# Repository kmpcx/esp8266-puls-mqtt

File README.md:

ESP8266 Sketch for potential free contact sensor
======================

This sketch is meant to let you detecd pulses on a potential free contact and send them via an asyncronous connection to a MQTT broker.
It can be used to monitor every kind of binary state. It can be used to detect machine cycles (counting parts), states of windows to observe if they are closed properly or any relay you can possibly think of.

## Table of content
- [Setup](#setup)
    - [WiFi](#wifi)
    - [MQTT](#mqtt)
    - [OTA](#ota)
- [PCB](#pcb)

## Setup

All the setup is done in the config file. You can create own config files for different locations/environment.

### WiFi

```
#define WIFI_SSID "SSID"
#define WIFI_PASSWORD "Password"

bool IPStatic = false; // true if it is a static IP
IPAddress staticIP(10,49,13,103); //ESP static ip
IPAddress gateway(10,49,13,1);   //IP Address of your WiFi Router (Gateway)
IPAddress subnet(255, 255, 255, 0);  //Subnet mask
IPAddress dns(10,49,13,1);  //DNS
```

### MQTT

You need to define your MQTT broker.
The MQTT Topics are defined in the main.ccp file.

```
#define MQTT_HOST IPAddress(0, 0, 0, 0)
#define MQTT_PORT 1883
#define MQTT_SECURE true
#define MQTT_USERNAME "USER"
#define MQTT_PASSWORD "PASSWORD"
```

### OTA

You need to define a location where the micro controller should ask for a update binary file.

```
#define updateServer "http://location.loc/"
```

## PCB

We designed a PCB board which fits perfectly the need for a potential free contact sensor.
The source for it is located in the PCB folder.

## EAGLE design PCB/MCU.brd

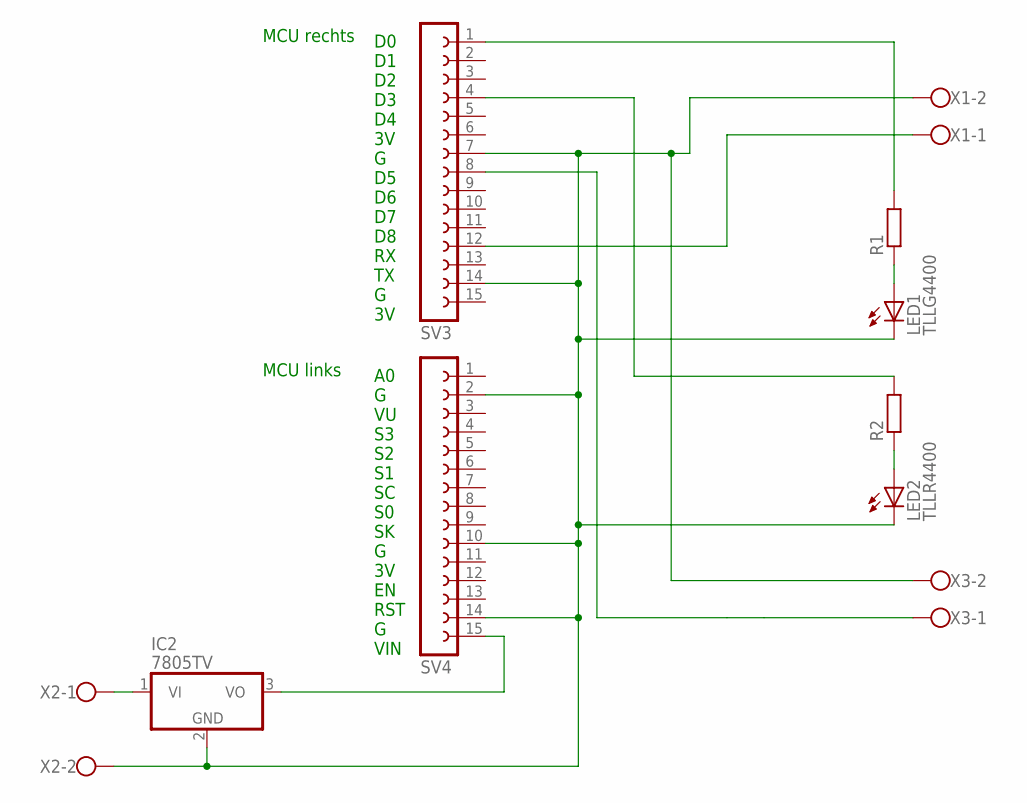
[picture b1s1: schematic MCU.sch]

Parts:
IC2: 7805TV; TO220V
LED1: TLLG4400; LED3MM
LED2: TLLR4400; LED3MM
R1, R2: R0207/10; 0207/10
SV3, SV4: FE15-1; FE15
X1, X2, X3: W237-102

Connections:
G: IC2.2 (GND), LED1.K (C), LED2.K (C), SV3.7, SV3.14, SV4.2, SV4.10, SV4.14, X1.2, X2.2, X3.2
unnamed: IC2.1 (VI), X2.1
unnamed: SV3.12, X1.1
unnamed: SV3.8, X3.1
unnamed: LED2.A, R2.1
unnamed: LED1.A, R1.1
unnamed: R1.2, SV3.1
unnamed: R2.2, SV3.4
unnamed: IC2.3 (VO), SV4.15

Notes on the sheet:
MCU rechts
MCU links
A0 G VU S3 S2 S1 SC S0 SK G 3V EN RST G VIN
D0 D1 D2 D3 D4 3V G D5 D6 D7 D8 RX TX G 3V

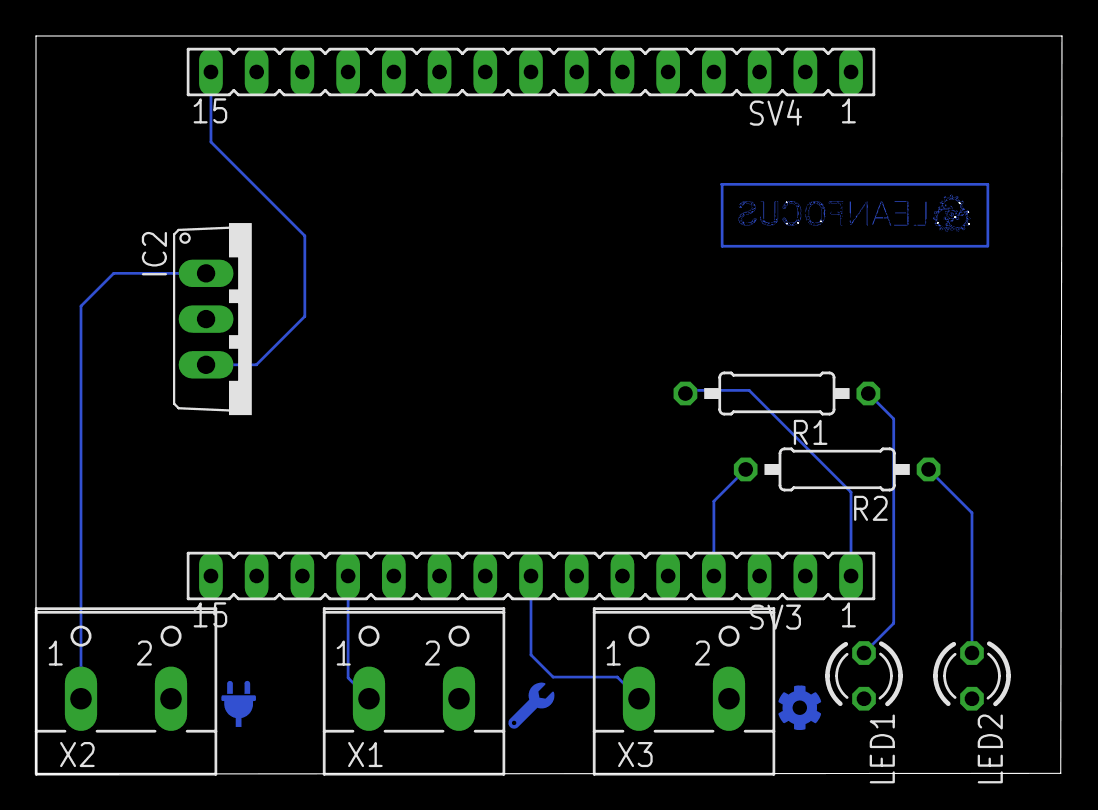
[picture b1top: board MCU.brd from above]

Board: 2 copper layers, 57.0 x 41.0 mm, 10 parts (0 on the bottom side), 9 nets.

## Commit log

2019-09-24 Test commit (README file)
2019-09-24 README commit
2019-09-24 Dependencies added
2019-09-24 Add platform version
2019-09-24 Add config_ABB
2019-09-24 Add ABB Env
2019-09-24 Rename kmpc
2019-09-25 Add configs for the other plants of Ringmetall
2019-09-25 Correction of the Configs
2019-09-25 Last correction
2019-09-25 Change Config ABB
2019-10-24 add cst server
2020-02-20 Add new CST Config
2020-03-09 Update versions
2020-03-09 Update configs to V16
2020-03-16 Adding Hanwha config
2020-03-19 Add RSSI option to send RSSI every 10 seconds
2020-03-19 Small fix
2020-03-19 Change heartbeat to RSSI
2020-03-20 Update ESPAsyncTCP
2020-03-24 Change version
2020-03-24 Simple LF Sensor Script
2020-03-24 Update SAL config
2020-04-03 Update config
2020-04-03 Revert "Update config"
    This reverts commit da56576c5776128ea6b1c1dc53d6eaed3ff09109
2020-04-03 Update core
2020-04-03 Include test version
2020-04-06 Remove old file
2020-04-15 Adjust config
2020-04-15 Restart if WiFi fails
2020-04-15 Change count for connect attempts
2020-04-16 Adjust reboot cycle
2020-04-16 Implement restart on connection failre
2020-04-16 Update version
2020-04-29 Update sketch
2020-04-30 Add SAL Ext and INT Config
2020-05-06 Version 20 Implement reset function for WiFi
2020-05-29 Add LICENSE
2020-05-29 Update LICENSE
2020-05-29 Add README.md
2020-05-29 Remove config files
2020-05-29 Adding PCB board to git
